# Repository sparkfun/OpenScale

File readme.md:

SparkFun OpenScale
===========================================================

[*SparkFun OpenScale (SEN-13261)*](https://www.sparkfun.com/products/13261)

The SparkFun OpenScale is a simple-to-use, open source solution for measuring weight and temperature. It has the ability to read multiple types of load cells and offers a simple-to-use serial menu to configure calibration value, sample rate, time stamp and units of precision.

Simply attach a four-wire or five-wire load cell of any capacity, plug the OpenScale into a USB port, open a terminal window at 9,600bps, and you’ll immediately see mass readings. The SparkFun OpenScale will enable you to turn a load cell or four load sensors in a Wheatstone bridge configuration into the DIY weigh scale for your application.

The OpenScale was designed for projects and applications where the load was static (like the beehive in front of SparkFun HQ) or where constant readings are needed without user intervention (for example, on a conveyor belt system). A load cell with an equipped OpenScale can remain in place for months without needing user interaction!

On board the SparkFun OpenScale is the ATmega328P microcontroller, for addressing your communications needs and transferring your data to a serial terminal or to a data logger such as the OpenLog, an FT231 with mini USB, for USB to serial connection; the HX711, a 24-bit ADC for weigh scales; and the TMP102, for recording the ambient temperature of your system. The OpenScale communicates at a TTL level of 9,600bps 8-N-1 by default and possesses a baud rate configurable from 1,200bps to 1,000,000bps.

You can read more about the beehive project that OpenScale is used in the [Internet of Bees](http://makezine.com/projects/bees-sensors-monitor-hive-health/) article.

Repository Contents
-------------------

* **/Documentation** - Images used in the hookup guide
* **/Production** - PCB panelized for production
* **/firmware** - Arduino sketch that runs on the ATmega328P
* **/hardware** - Eagle files

Documentation
--------------

* **[Installing an Arduino Library Guide](https://learn.sparkfun.com/tutorials/installing-an-arduino-library)** - Basic information on how to install an Arduino library.
* **[Hookup Guide](https://learn.sparkfun.com/tutorials/openscale-applications-and-hookup-guide)** - Basic hookup guide for the SparkFun OpenScale

License Information
-------------------

This product is _**open source**_! 

Various bits of the code have different licenses applied. Anything SparkFun wrote is beerware; if you see me (or any other SparkFun employee) at the local, and you've found our code helpful, please buy us a round!

Please use, reuse, and modify these files as you see fit. Please maintain attribution to SparkFun Electronics and release anything derivative under the same license.

Distributed as-is; no warranty is given.

- Your friends at SparkFun.

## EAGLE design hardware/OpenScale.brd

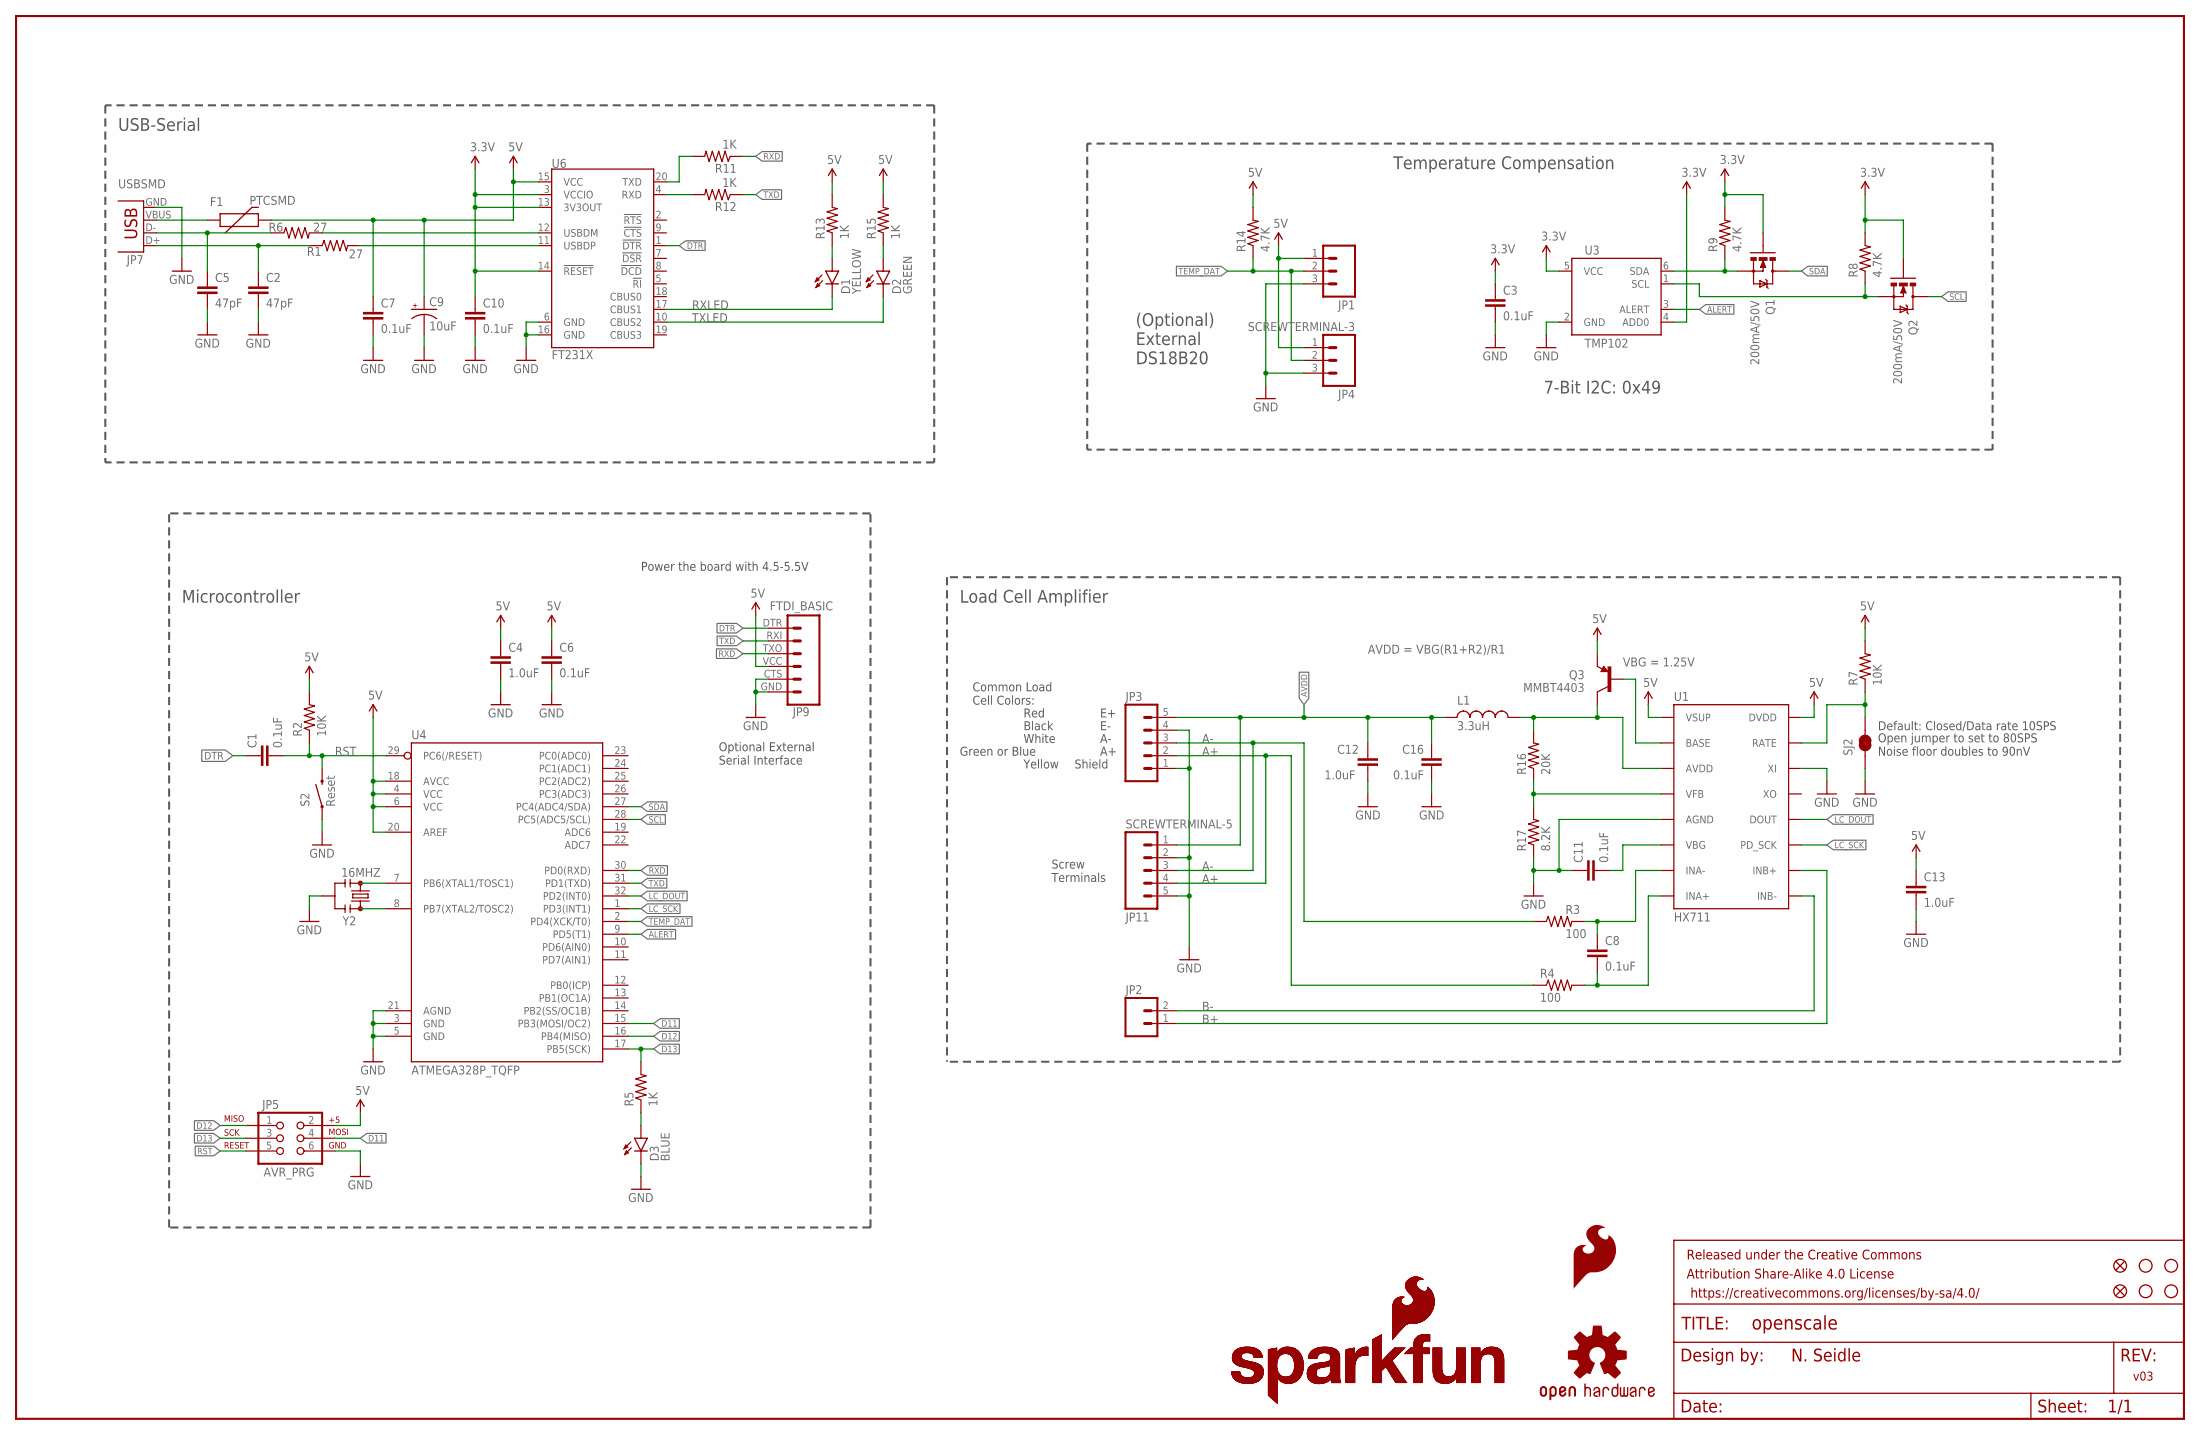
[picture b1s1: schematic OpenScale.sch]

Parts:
C1, C3, C6, C7, C8, C10, C11, C16: 0.1uF; 0603-CAP
C2, C5: 47pF; 0603-CAP
C4, C12, C13: 1.0uF; 0603-CAP
C9: 10uF; EIA3216
D1: YELLOW; LED-1206
D2: GREEN; LED-1206
D3: BLUE; LED-1206
F1: PTCSMD; PTC-1206
FID1, FID2: FIDUCIAL1X2; FIDUCIAL-1X2
FRAME1: FRAME-LEDGER; CREATIVE_COMMONS
JP1: M031X03_NO_SILK; 1X03_NO_SILK
JP2: M02PTH; 1X02
JP3: M05NO_SILK; 1X05_NO_SILK
JP4: SCREWTERMINAL-3; SCREWTERMINAL-3.5MM-3_LOCK.007S
JP5: AVR_PRG; 2X3
JP7: USBSMD; USB-MINIB
JP9: FTDI_BASIC
JP11: SCREWTERMINAL-5; SCREWTERMINAL-3.5MM-5
L1: 3.3uH; 0805
LOGO1, LOGO4: SFE_LOGO_NAME_FLAME.1_INCH; SFE_LOGO_NAME_FLAME_.1
LOGO2: OSHW-LOGOS; OSHW-LOGO-S
LOGO3: SFE_LOGO_FLAME.1_STOP; SFE_LOGO_FLAME_STOP_.1
Q1, Q2: 200mA/50V; SOT23-3
Q3: MMBT4403; SOT23-3
R1, R6: 27; 0603
R2, R7: 10K; 0603-RES
R3, R4: 100; 0603-RES
R5, R11, R12, R13, R15: 1K; 0603-RES
R8, R9, R14: 4.7K; 0603-RES
R16: 20K; 0603-RES
R17: 8.2K; 0603-RES
S2: Reset; TACTILE-SWITCH-1101NE
SJ2: JUMPER-PAD-2-NC_BY_TRACE; PAD-JUMPER-2-NC_BY_TRACE_YES_SILK
STANDOFF1, STANDOFF2, STANDOFF3, STANDOFF4: STAND-OFF
U1: HX711; SO16
U3: TMP102; SOT563
U4: ATMEGA328P_TQFP; TQFP32-08
U6: FT231X; SSOP20_L
Y2: 16MHZ; RESONATOR-SMD

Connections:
3.3V: C3.1, C10.1, Q1.1 (G), Q2.1 (G), R8.2, R9.2, U3.4 (ADD0), U3.5 (VCC), U6.3 (VCCIO), U6.13 (3V3OUT), U6.14 (!RESET)
5V: C4.1, C6.1, C7.1, C9.A (+), C13.1, F1.2, JP1.1, JP4.1, JP5.2, JP9.VCC (4), Q3.2 (E), R2.2, R7.2, R13.2, R14.2, R15.2, U1.1 (VSUP), U1.16 (DVDD), U4.4 (VCC), U4.6 (VCC), U4.18 (AVCC), U4.20 (AREF), U6.15 (VCC)
A+: JP3.2, JP11.4, R4.1
A-: JP3.3, JP11.3, R3.1
ALERT: U3.3 (ALERT), U4.9 (PD5(T1))
AVDD: C12.2, C16.1, JP3.5, JP11.1, L1.1
B+: JP2.1, U1.10 (INB+)
B-: JP2.2, U1.9 (INB-)
D11: JP5.4, U4.15 (PB3(MOSI/OC2))
D12: JP5.1, U4.16 (PB4(MISO))
D13: JP5.3, R5.2, U4.17 (PB5(SCK))
DTR: C1.1, JP9.DTR (1), U6.1 (!DTR)
GND: C2.2, C3.2, C4.2, C5.2, C6.2, C7.2, C9.C (-), C10.2, C11.1, C12.1, C13.2, C16.2, D3.C, JP1.3, JP3.1, JP3.4, JP4.3, JP5.6, JP7.GND, JP9.CTS (5), JP9.GND (6), JP11.2, JP11.5, R17.1, S2.1, SJ2.1, U1.5 (AGND), U1.14 (XI), U3.2 (GND), U4.3 (GND), U4.5 (GND), U4.21 (AGND), U6.6 (GND), U6.16 (GND), Y2.2
LC_DOUT: U1.12 (DOUT), U4.32 (PD2(INT0))
LC_SCK: U1.11 (PD_SCK), U4.1 (PD3(INT1))
LV_SCL: Q2.2 (S), R8.1, U3.1 (SCL)
LV_SDA: Q1.2 (S), R9.1, U3.6 (SDA)
unnamed: U4.7 (PB6(XTAL1/TOSC1)), Y2.1
unnamed: D3.A, R5.1
unnamed: U4.8 (PB7(XTAL2/TOSC2)), Y2.3
unnamed: C5.1, JP7.D-, R6.1
unnamed: D1.A, R13.1
unnamed: D2.A, R15.1
unnamed: C2.1, JP7.D+, R1.1
unnamed: R6.2, U6.12 (USBDM)
unnamed: R7.1, SJ2.2, U1.15 (RATE)
unnamed: C8.1, R3.2, U1.7 (INA-)
unnamed: C8.2, R4.2, U1.8 (INA+)
unnamed: F1.1, JP7.VBUS
unnamed: R1.2, U6.11 (USBDP)
unnamed: R12.2, U6.4 (RXD)
unnamed: L1.2, Q3.3 (C), R16.2, U1.3 (AVDD)
unnamed: R11.2, U6.20 (TXD)
unnamed: Q3.1 (B), U1.2 (BASE)
unnamed: R16.1, R17.2, U1.4 (VFB)
unnamed: C11.2, U1.6 (VBG)
RST: C1.2, JP5.5, R2.1, S2.2, U4.29 (PC6(/RESET))
RXD: JP9.TXO (3), R11.1, U4.30 (PD0(RXD))
RXLED: D1.C, U6.17 (CBUS1)
SCL: Q2.3 (D), U4.28 (PC5(ADC5/SCL))
SDA: Q1.3 (D), U4.27 (PC4(ADC4/SDA))
TEMP_DAT: JP1.2, JP4.2, R14.1, U4.2 (PD4(XCK/T0))
TXD: JP9.RXI (2), R12.1, U4.31 (PD1(TXD))
TXLED: D2.C, U6.10 (CBUS2)

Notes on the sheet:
Microcontroller
USB-Serial
Default: Closed/Data rate 10SPS
Open jumper to set to 80SPS Noise floor doubles to 90nV
Red
Black
White
Green or Blue
Common Load Cell Colors:
Temperature Compensation
(Optional) External DS18B20
Load Cell Amplifier
7-Bit I2C: 0x49
Screw Terminals
Yellow
Shield
Optional External Serial Interface
VBG = 1.25V
AVDD = VBG(R1+R2)/R1
v03
N. Seidle
Power the board with 4.5-5.5V

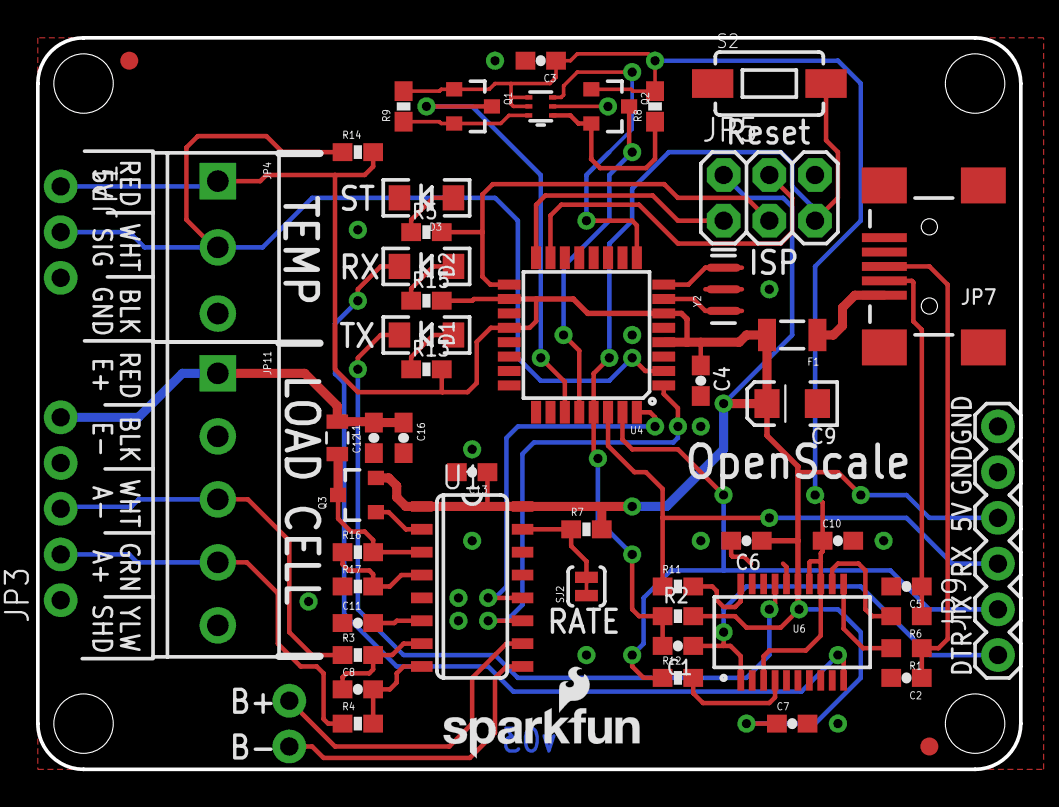
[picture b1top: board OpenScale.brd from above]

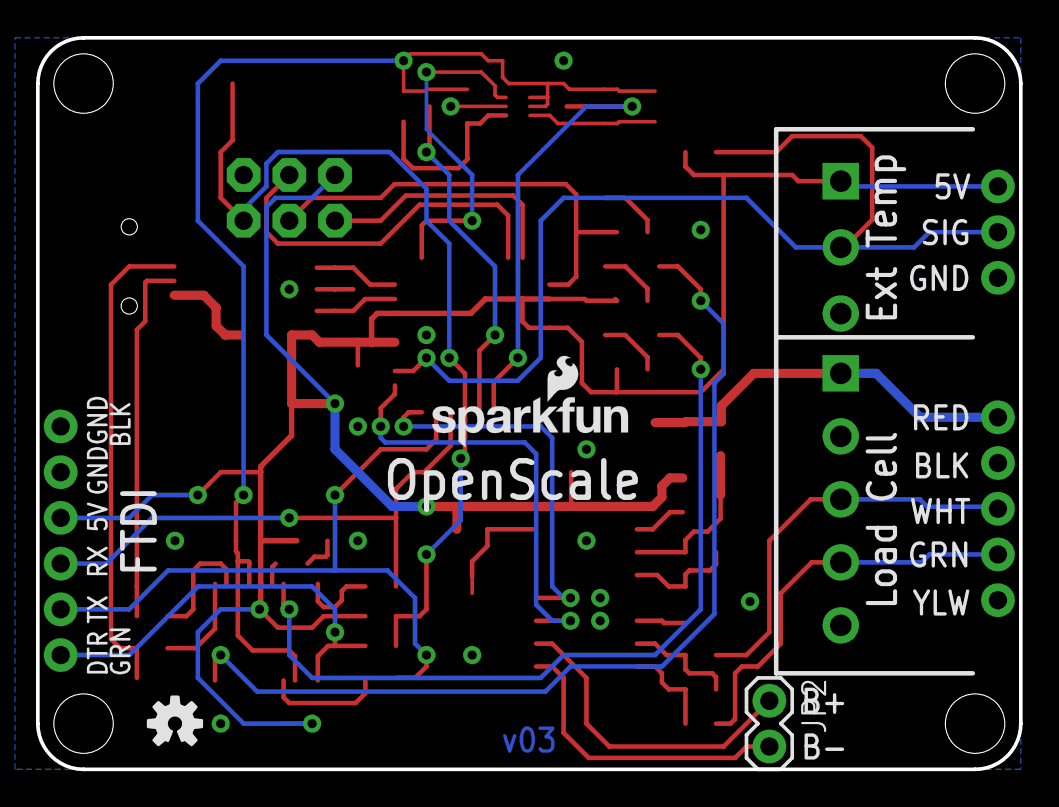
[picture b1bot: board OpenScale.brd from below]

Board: 2 copper layers, 54.6 x 40.6 mm, 64 parts (3 on the bottom side), 44 nets.

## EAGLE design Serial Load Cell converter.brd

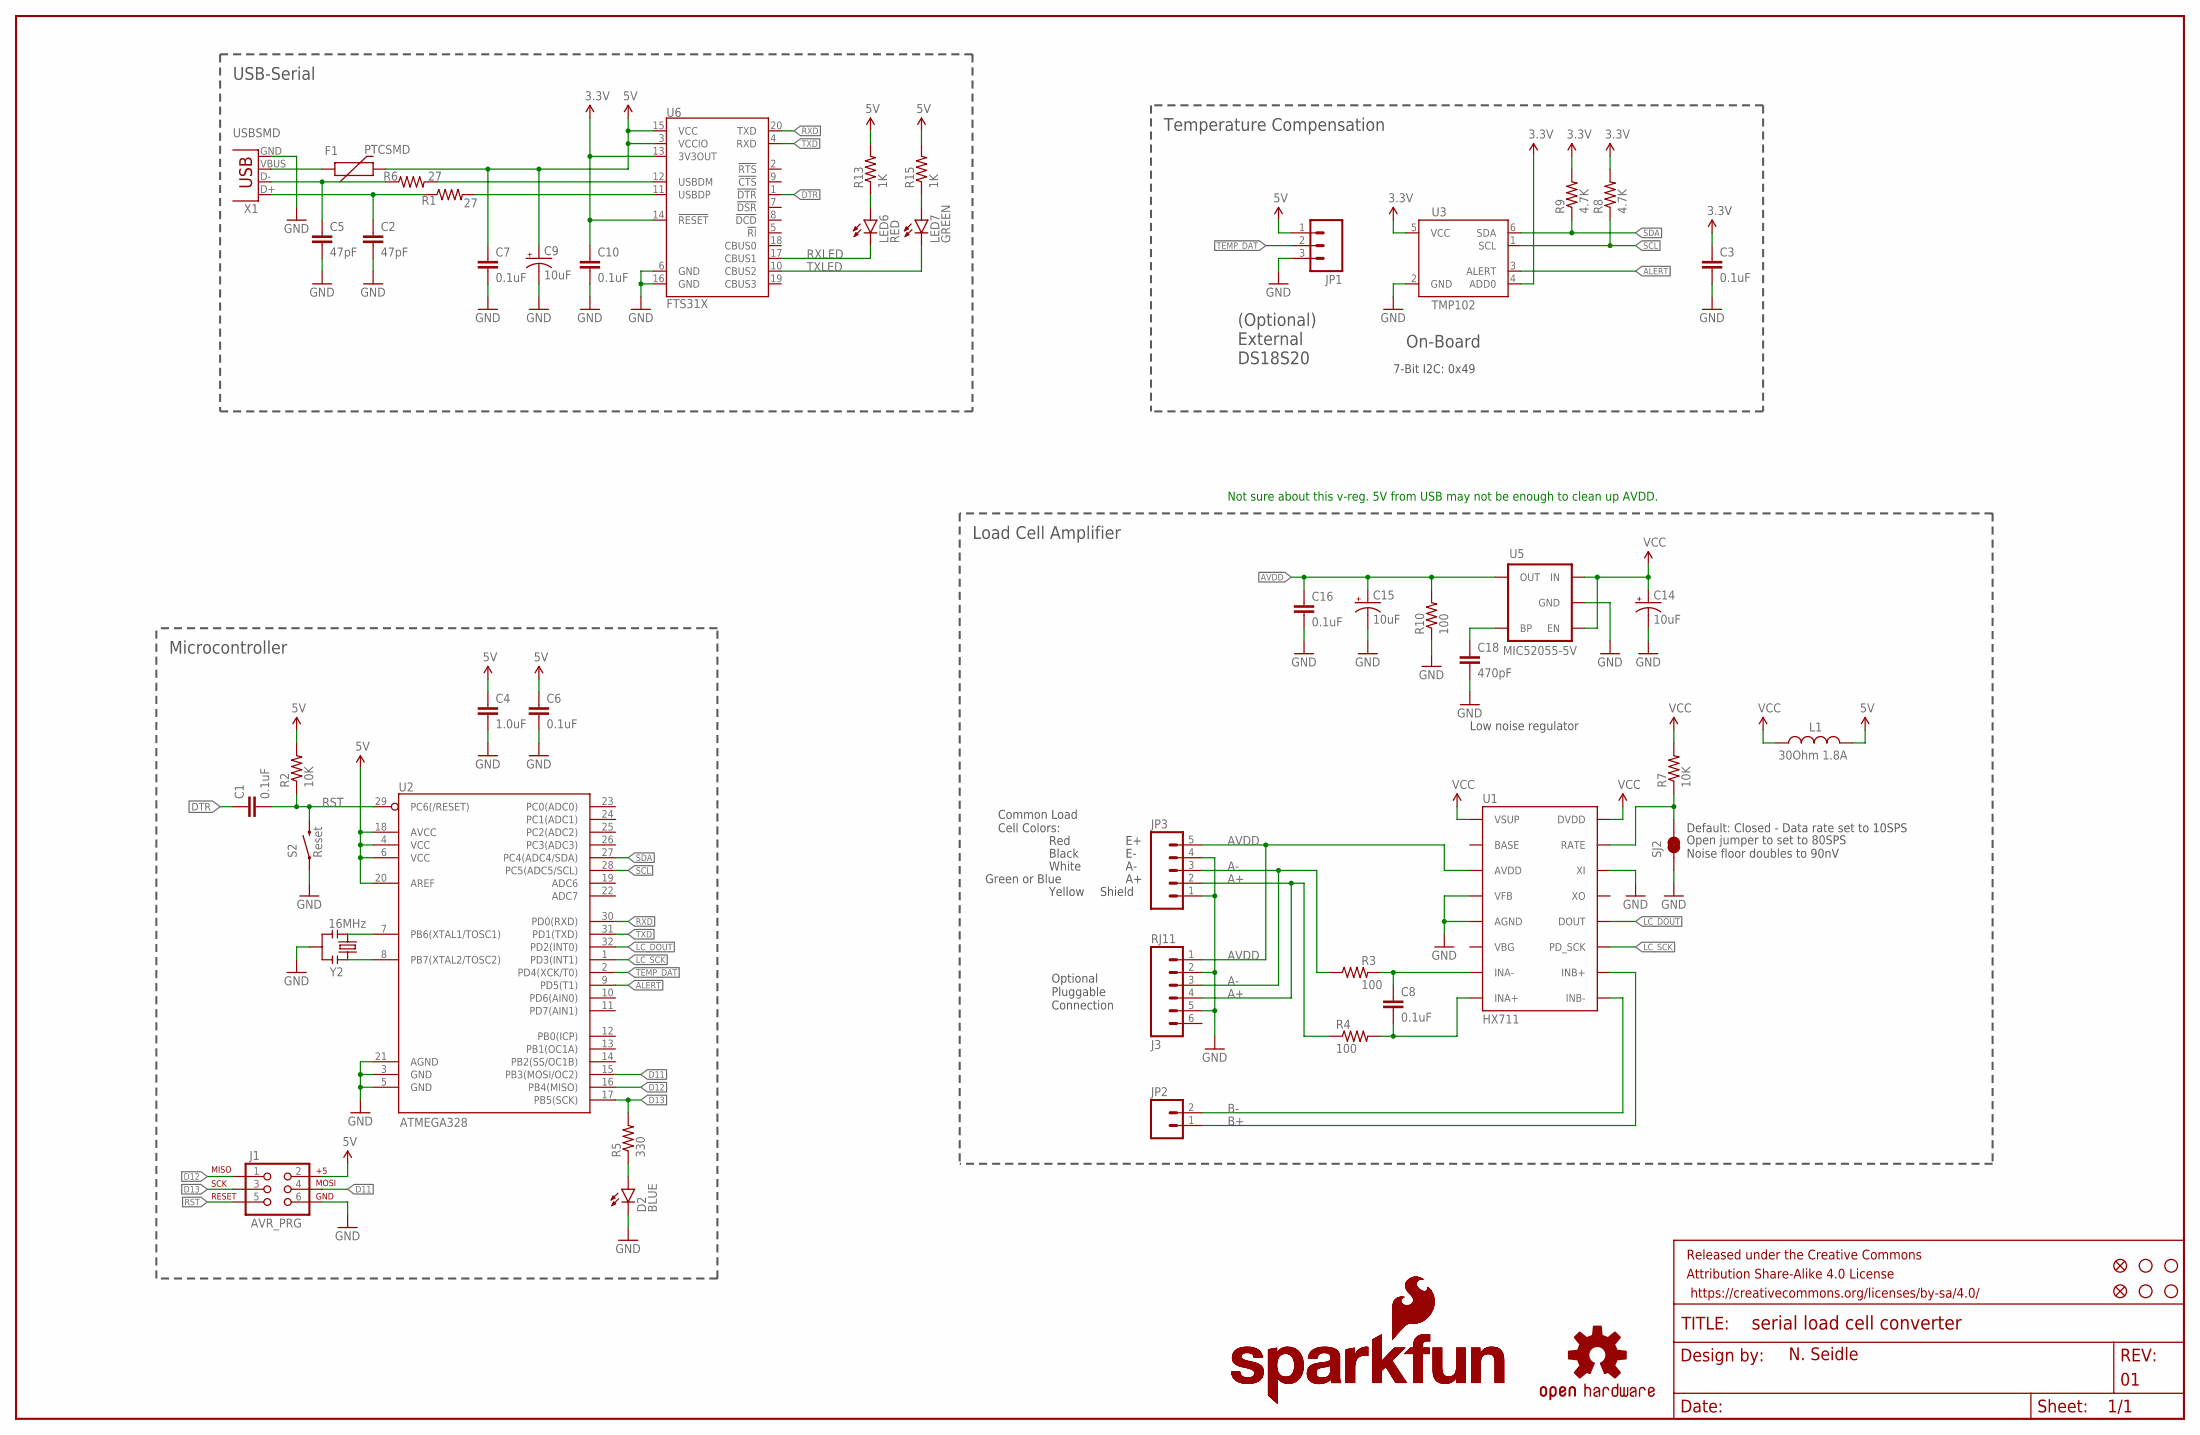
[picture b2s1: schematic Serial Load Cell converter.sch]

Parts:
C1, C3, C6, C7, C8, C10, C16: 0.1uF; 0603-CAP
C2, C5: 47pF; 0603-CAP
C4: 1.0uF; 0603-CAP
C9, C14, C15: 10uF; EIA3216
C18: 470pF; 0603-CAP
D2: BLUE; LED-1206
F1: PTCSMD; PTC-1206
FID1, FID2: FIDUCIAL1X2; FIDUCIAL-1X2
FRAME1: FRAME-LEDGER; CREATIVE_COMMONS
J1: AVR_PRG; 2X3
J3: RJ11; RJ11-6
JP1: M03PTH; 1X03
JP2: M02PTH; 1X02
JP3: M05PTH; 1X05
L1: 30Ohm 1.8A; 0603
LED6: RED; LED-1206
LED7: GREEN; LED-1206
LOGO1, LOGO4: SFE_LOGO_NAME_FLAME.1_INCH; SFE_LOGO_NAME_FLAME_.1
LOGO2: OSHW-LOGOS; OSHW-LOGO-S
R1, R6: 27; 0603
R2, R7: 10K; 0603-RES
R3, R4, R10: 100; 0603-RES
R5: 330; 0603-RES
R8, R9: 4.7K; 0603-RES
R13, R15: 1K; 0603-RES
S2: Reset; TACTILE-SWITCH-SMD
SJ2: JUMPER-PAD-2-NC_BY_TRACE; PAD-JUMPER-2-NC_BY_TRACE_YES_SILK
STANDOFF1, STANDOFF2, STANDOFF3, STANDOFF4: STAND-OFF
U1: HX711; SO16
U2: ATMEGA328; TQFP32-08
U3: TMP102; SOT563
U5: MIC52055-5V; SOT23-5
U6: FTS31X; SSOP20_L
X1: USBSMD; USB-MINIB
Y2: 16MHz; RESONATOR-SMD

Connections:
3.3V: C3.1, C10.1, R8.2, R9.2, U3.4 (ADD0), U3.5 (VCC), U6.13 (3V3OUT), U6.14 (!RESET)
5V: C4.1, C6.1, C7.1, C9.A (+), F1.2, J1.2, JP1.1, L1.2, R2.2, R13.2, R15.2, U2.4 (VCC), U2.6 (VCC), U2.18 (AVCC), U2.20 (AREF), U6.3 (VCCIO), U6.15 (VCC)
A+: J3.4, JP3.2, R4.1
A-: J3.3, JP3.3, R3.1
ALERT: U2.9 (PD5(T1)), U3.3 (ALERT)
AVDD: C15.A (+), C16.1, J3.1, JP3.5, R10.2, U1.3 (AVDD), U5.5 (OUT)
B+: JP2.1, U1.10 (INB+)
B-: JP2.2, U1.9 (INB-)
D11: J1.4, U2.15 (PB3(MOSI/OC2))
D12: J1.1, U2.16 (PB4(MISO))
D13: J1.3, R5.2, U2.17 (PB5(SCK))
DTR: C1.1, U6.1 (!DTR)
GND: C2.2, C3.2, C4.2, C5.2, C6.2, C7.2, C9.C (-), C10.2, C14.C (-), C15.C (-), C16.2, C18.2, D2.C, J1.6, J3.2, J3.5, JP1.3, JP3.1, JP3.4, R10.1, S2.1, SJ2.1, U1.4 (VFB), U1.5 (AGND), U1.14 (XI), U2.3 (GND), U2.5 (GND), U2.21 (AGND), U3.2 (GND), U5.2 (GND), U6.6 (GND), U6.16 (GND), X1.GND, Y2.2
LC_DOUT: U1.12 (DOUT), U2.32 (PD2(INT0))
LC_SCK: U1.11 (PD_SCK), U2.1 (PD3(INT1))
unnamed: U2.7 (PB6(XTAL1/TOSC1)), Y2.1
unnamed: D2.A, R5.1
unnamed: U2.8 (PB7(XTAL2/TOSC2)), Y2.3
unnamed: C5.1, R6.1, X1.D-
unnamed: LED6.A, R13.1
unnamed: LED7.A, R15.1
unnamed: C2.1, R1.1, X1.D+
unnamed: R6.2, U6.12 (USBDM)
unnamed: R7.1, SJ2.2, U1.15 (RATE)
unnamed: C8.1, R3.2, U1.7 (INA-)
unnamed: C8.2, R4.2, U1.8 (INA+)
unnamed: F1.1, X1.VBUS
unnamed: R1.2, U6.11 (USBDP)
unnamed: C18.1, U5.4 (BP)
RST: C1.2, J1.5, R2.1, S2.3 (2), U2.29 (PC6(/RESET))
RXD: U2.30 (PD0(RXD)), U6.20 (TXD)
RXLED: LED6.C, U6.17 (CBUS1)
SCL: R8.1, U2.28 (PC5(ADC5/SCL)), U3.1 (SCL)
SDA: R9.1, U2.27 (PC4(ADC4/SDA)), U3.6 (SDA)
TEMP_DAT: JP1.2, U2.2 (PD4(XCK/T0))
TXD: U2.31 (PD1(TXD)), U6.4 (RXD)
TXLED: LED7.C, U6.10 (CBUS2)
VCC: C14.A (+), L1.1, R7.2, U1.1 (VSUP), U1.16 (DVDD), U5.1 (IN), U5.3 (EN)

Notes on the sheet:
Microcontroller
USB-Serial
Default: Closed - Data rate set to 10SPS
Open jumper to set to 80SPS Noise floor doubles to 90nV
Red
Black
White
Green or Blue
Common Load Cell Colors:
Temperature Compensation
(Optional) External DS18S20
On-Board
Load Cell Amplifier
7-Bit I2C: 0x49
Optional Pluggable Connection
Yellow
Shield
Not sure about this v-reg. 5V from USB may not be enough to clean up AVDD.
Low noise regulator

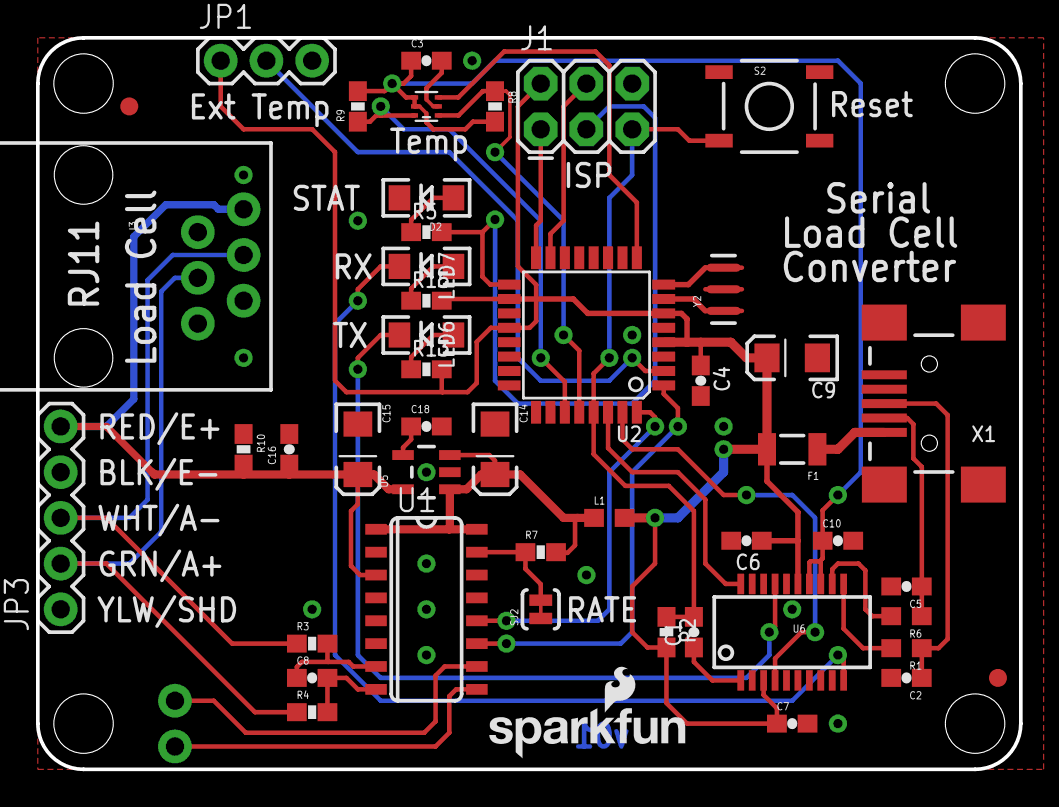
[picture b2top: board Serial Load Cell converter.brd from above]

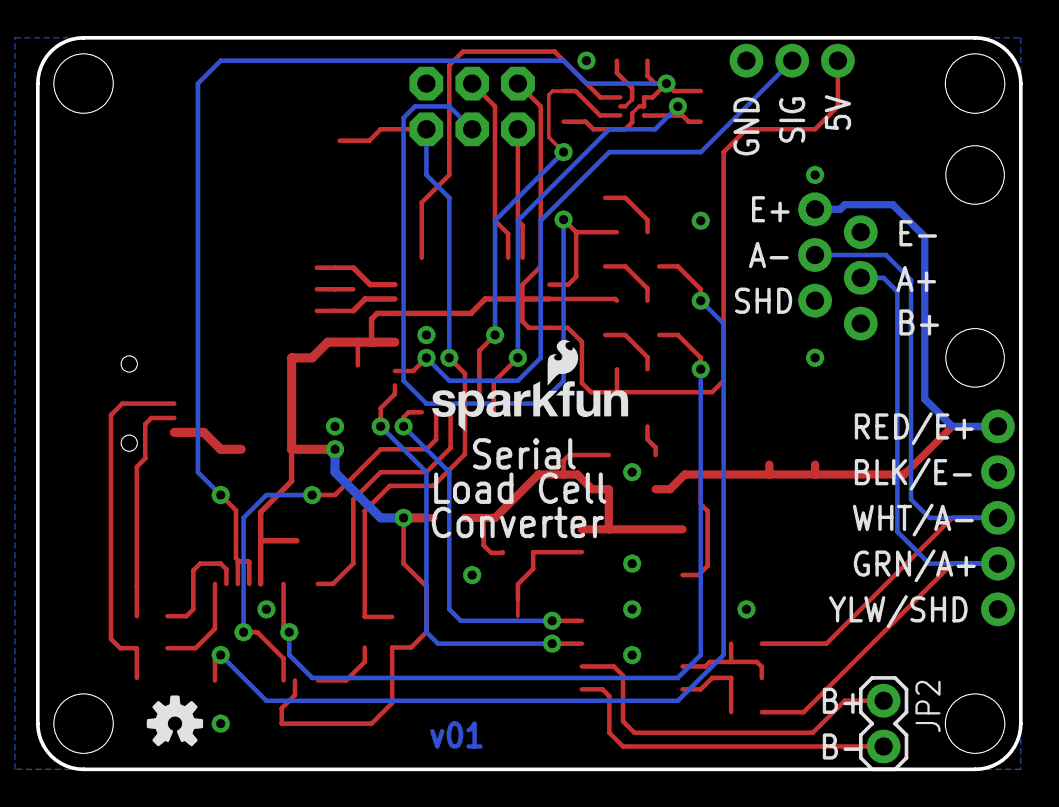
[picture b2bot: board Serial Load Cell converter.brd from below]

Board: 2 copper layers, 54.6 x 40.6 mm, 55 parts (3 on the bottom side), 38 nets.

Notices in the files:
parts and their libraries:
SparkFun-Aesthetics: Licensing: CC v3.0 Share-Alike You are welcome to use this library for commercial purposes.
SparkFun-Resistors: Licensing: Creative Commons ShareAlike 4.0 International - https://creativecommons.org/licenses/by-sa/4.0
SparkFun-Aesthetics: Released under the Creative Commons
